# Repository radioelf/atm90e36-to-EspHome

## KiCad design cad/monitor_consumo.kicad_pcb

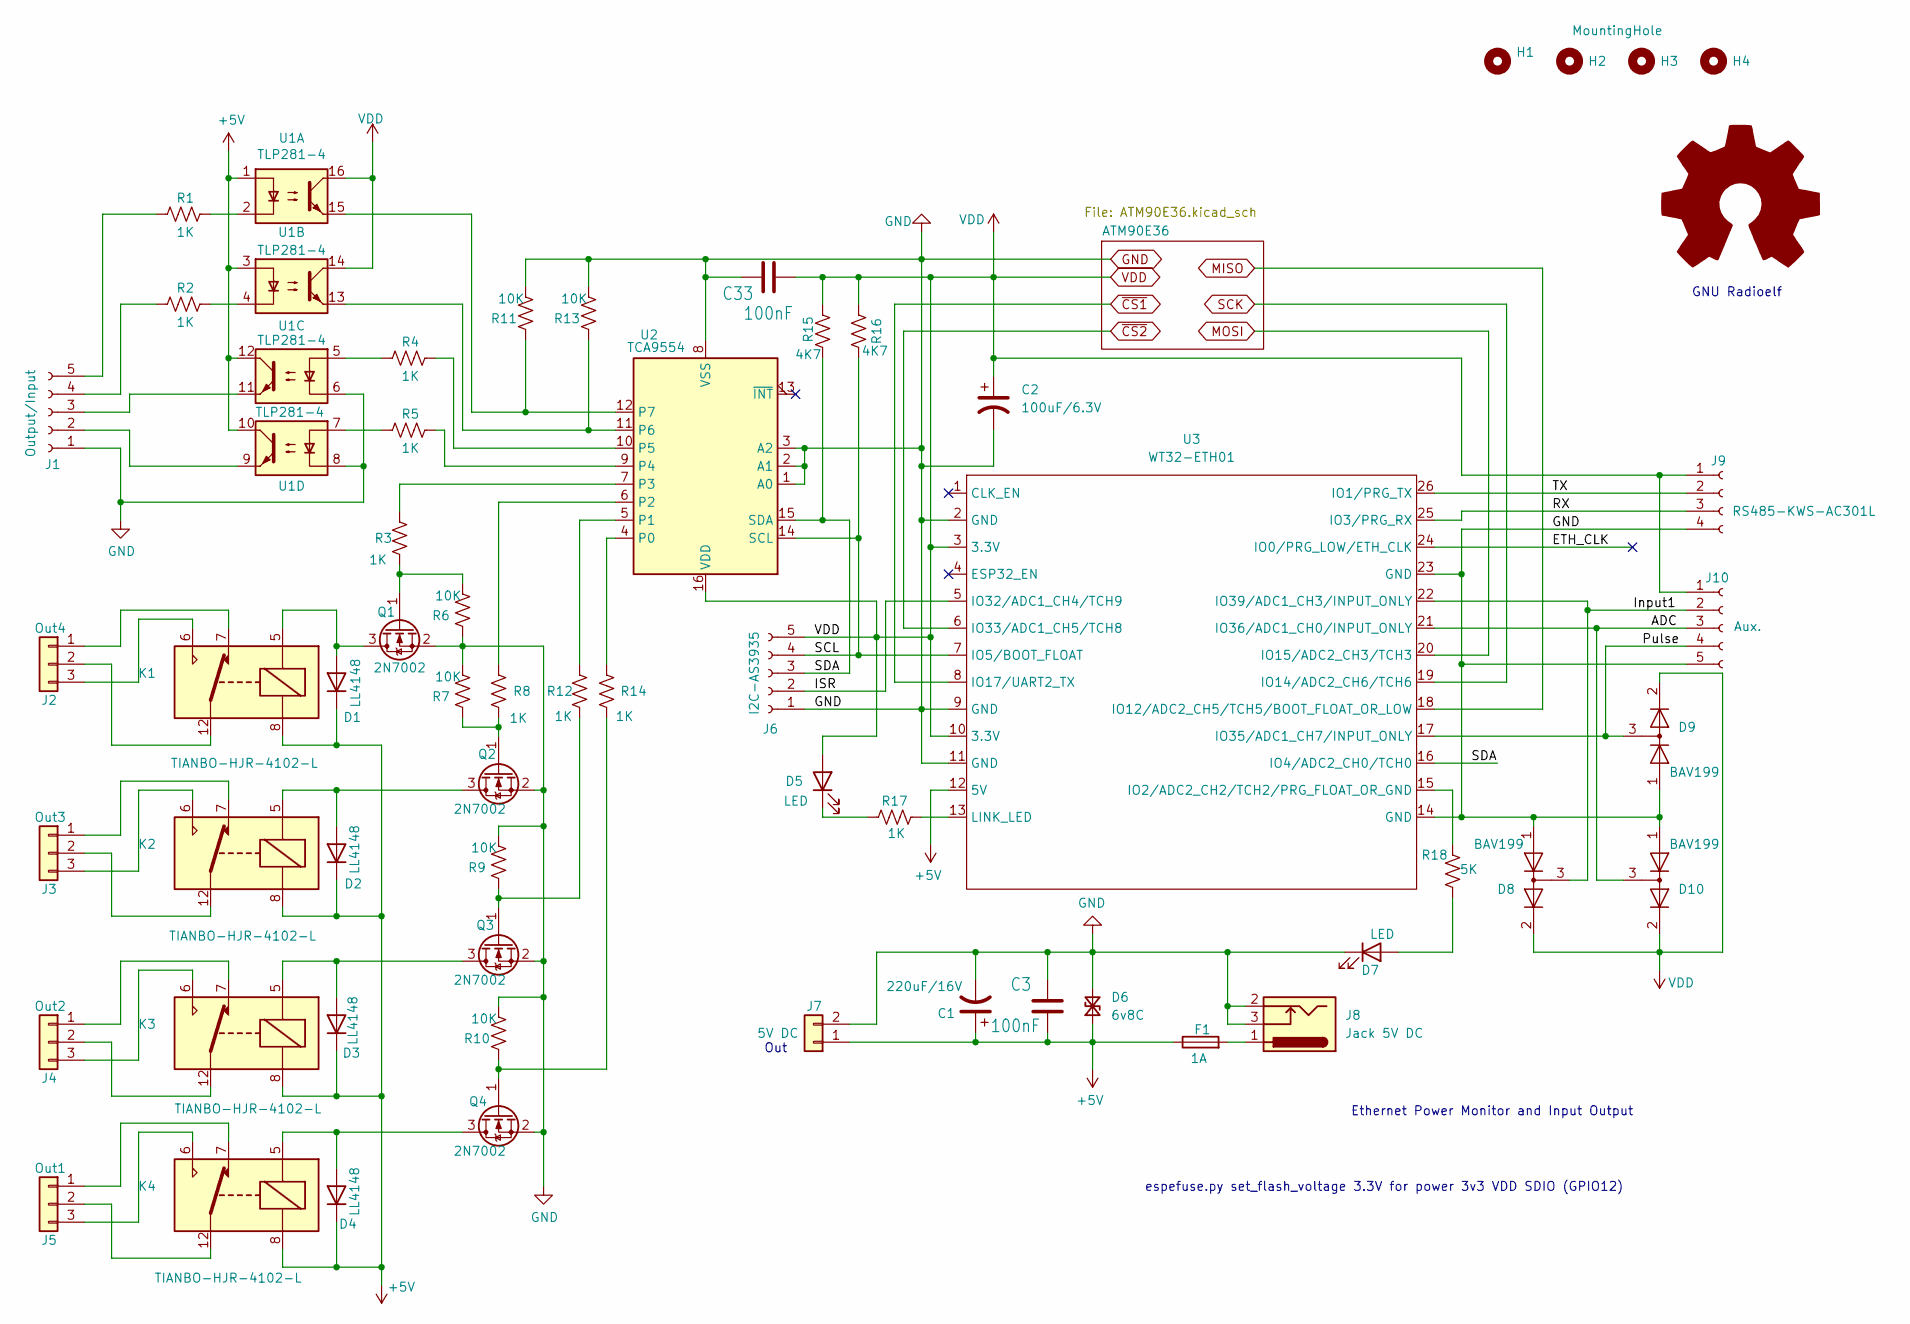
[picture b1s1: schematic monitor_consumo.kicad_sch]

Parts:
C1: 220uF/16V; CP_Elec_8x5.4
C2: 100uF/6.3V; CP_Elec_4x5.4
C3, C33: 100nF; C0603
D1, D2, D3, D4: LL4148; D_MiniMELF
D5, D7: LED; LED_0603_1608Metric
D6: 6v8C; D_SMB
D8, D9, D10: BAV199; SOT-23
F1: 1A; Fuseholder_TR5_Littelfuse_No560_No460
H1, H2, H3, H4: MountingHole; MountingHole_3.2mm_M3
J1: Output/Input; PinHeader_1x05_P2.54mm_Vertical
J2: Out4; TerminalBlock_Phoenix_PT-1,5-3-3.5-H_1x03_P3.50mm_Horizontal
J3: Out3; TerminalBlock_Phoenix_PT-1,5-3-3.5-H_1x03_P3.50mm_Horizontal
J4: Out2; TerminalBlock_Phoenix_PT-1,5-3-3.5-H_1x03_P3.50mm_Horizontal
J5: Out1; TerminalBlock_Phoenix_PT-1,5-3-3.5-H_1x03_P3.50mm_Horizontal
J6: I2C-AS3935; PinHeader_1x05_P2.54mm_Vertical
J7: 5V DC; JST_NV_B02P-NV_1x02_P5.00mm_Vertical
J8: Jack 5V DC; BarrelJack_GCT_DCJ200-10-A_Horizontal
J9: RS485-KWS-AC301L; PinHeader_1x04_P2.54mm_Vertical
J10: Aux.; PinHeader_1x05_P2.54mm_Vertical
K1, K2, K3, K4: TIANBO-HJR-4102-L; Relay_SPDT_HJR-4102
Q1, Q2, Q3, Q4: 2N7002; 2N7002-SOT95P240X111-3N
R1, R2, R3, R4, R5, R8, R12, R14, R17: 1K; R0603
R6, R7, R9, R10, R11, R13: 10K; R0603
R15, R16: 4K7; R0603
R18: 5K; R0603
U1: TLP281-4; SOIC127P700X210-16N
U2: TCA9554; SOIC-16W_7.5x10.3mm_P1.27mm
U3: WT32-ETH01

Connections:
+5V: C1.1, C3.2, D1.1 (K), D2.1 (K), D3.1 (K), D4.1 (K), D6.1 (A1), F1.1, J7.1, K1.8, K2.8, K3.8, K4.8, U1.1, U1.3, U1.10, U1.12, U3.12 (5V)
/ADC: D10.3 (K), J10.3, U3.21 (IO36/ADC1_CH0/INPUT_ONLY)
/ETH_CLK: U3.24 (IO0/PRG_LOW/ETH_CLK)
/ISR: J6.2, U3.5 (IO32/ADC1_CH4/TCH9)
/Input1: D8.3 (K), J10.2, U3.22 (IO39/ADC1_CH3/INPUT_ONLY)
/Pulse: D9.3 (K), J10.4, U3.17 (IO35/ADC1_CH7/INPUT_ONLY)
/RX: J9.3, U3.25 (IO3/PRG_RX)
/SCL: J6.4, R16.1, U2.14 (SCL), U3.7 (IO5/BOOT_FLOAT)
/SDA: J6.3, R15.1, U2.15 (SDA), U3.16 (IO4/ADC2_CH0/TCH0)
/TX: J9.2, U3.26 (IO1/PRG_TX)
GND: C1.2, C2.2, C3.1, C33.1, D6.2 (A2), D7.1 (K), D8.1 (K), D9.1 (K), D10.1 (K), J1.1, J6.1, J7.2, J8.2, J8.3, J9.4, J10.5, Q1.2 (S), Q2.2 (S), Q3.2 (S), Q4.2 (S), R6.1, R7.2, R9.2, R10.2, R11.2, R13.2, U1.6, U1.8, U2.1 (A0), U2.2 (A1), U2.3 (A2), U2.8 (VSS), U3.2 (GND), U3.9 (GND), U3.11 (GND), U3.14 (GND), U3.23 (GND); also elsewhere on the board
MISO: U3.18 (IO12/ADC2_CH5/TCH5/BOOT_FLOAT_OR_LOW); also elsewhere on the board
MOSI: U3.20 (IO15/ADC2_CH3/TCH3); also elsewhere on the board
unnamed: D1.2 (A), K1.5, Q1.3 (D)
unnamed: D2.2 (A), K2.5, Q2.3 (D)
unnamed: D3.2 (A), K3.5, Q3.3 (D)
unnamed: D4.2 (A), K4.5, Q4.3 (D)
unnamed: D5.1 (K), R17.1
unnamed: D7.2 (A), R18.1
unnamed: F1.2, J8.1
unnamed: J1.2, U1.9
unnamed: J1.3, U1.11
unnamed: J1.4, R2.2
unnamed: J1.5, R1.2
unnamed: J2.1, K1.7
unnamed: J2.2, K1.1, K1.12
unnamed: J2.3, K1.6
unnamed: J3.1, K2.7
unnamed: J3.2, K2.1, K2.12
unnamed: J3.3, K2.6
unnamed: J4.1, K3.7
unnamed: J4.2, K3.1, K3.12
unnamed: J4.3, K3.6
unnamed: J5.1, K4.7
unnamed: J5.2, K4.1, K4.12
unnamed: J5.3, K4.6
unnamed: Q1.1 (G), R3.1, R6.2
unnamed: Q2.1 (G), R7.1, R8.1
unnamed: Q3.1 (G), R9.1, R12.1
unnamed: Q4.1 (G), R10.1, R14.1
unnamed: R1.1, U1.2
unnamed: R2.1, U1.4
unnamed: R4.2, U1.5
unnamed: R5.2, U1.7
unnamed: R14.2, U2.4 (P0)
unnamed: R12.2, U2.5 (P1)
unnamed: R8.2, U2.6 (P2)
unnamed: R3.2, U2.7 (P3)
unnamed: R5.1, U2.9 (P4)
unnamed: R4.1, U2.10 (P5)
unnamed: R13.1, U1.13, U2.11 (P6)
unnamed: R11.1, U1.15, U2.12 (P7)
unnamed: R18.2, U3.15 (IO2/ADC2_CH2/TCH2/PRG_FLOAT_OR_GND)
unnamed: R17.2, U3.13 (LINK_LED)
SCK: U3.19 (IO14/ADC2_CH6/TCH6); also elsewhere on the board
VDD: C2.1, C33.2, D5.2 (A), D8.2 (A), D9.2 (A), D10.2 (A), J6.5, J9.1, J10.1, R15.2, R16.2, U1.14, U1.16, U2.16 (VDD), U3.3 (3.3V), U3.10 (3.3V); also elsewhere on the board
~CS1: U3.8 (IO17/UART2_TX); also elsewhere on the board
~CS2: U3.6 (IO33/ADC1_CH5/TCH8); also elsewhere on the board

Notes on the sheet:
GNU Radioelf
espefuse.py set_flash_voltage 3.3V for power 3v3 VDD SDIO (GPIO12)
Out
Ethernet Power Monitor and Input Output

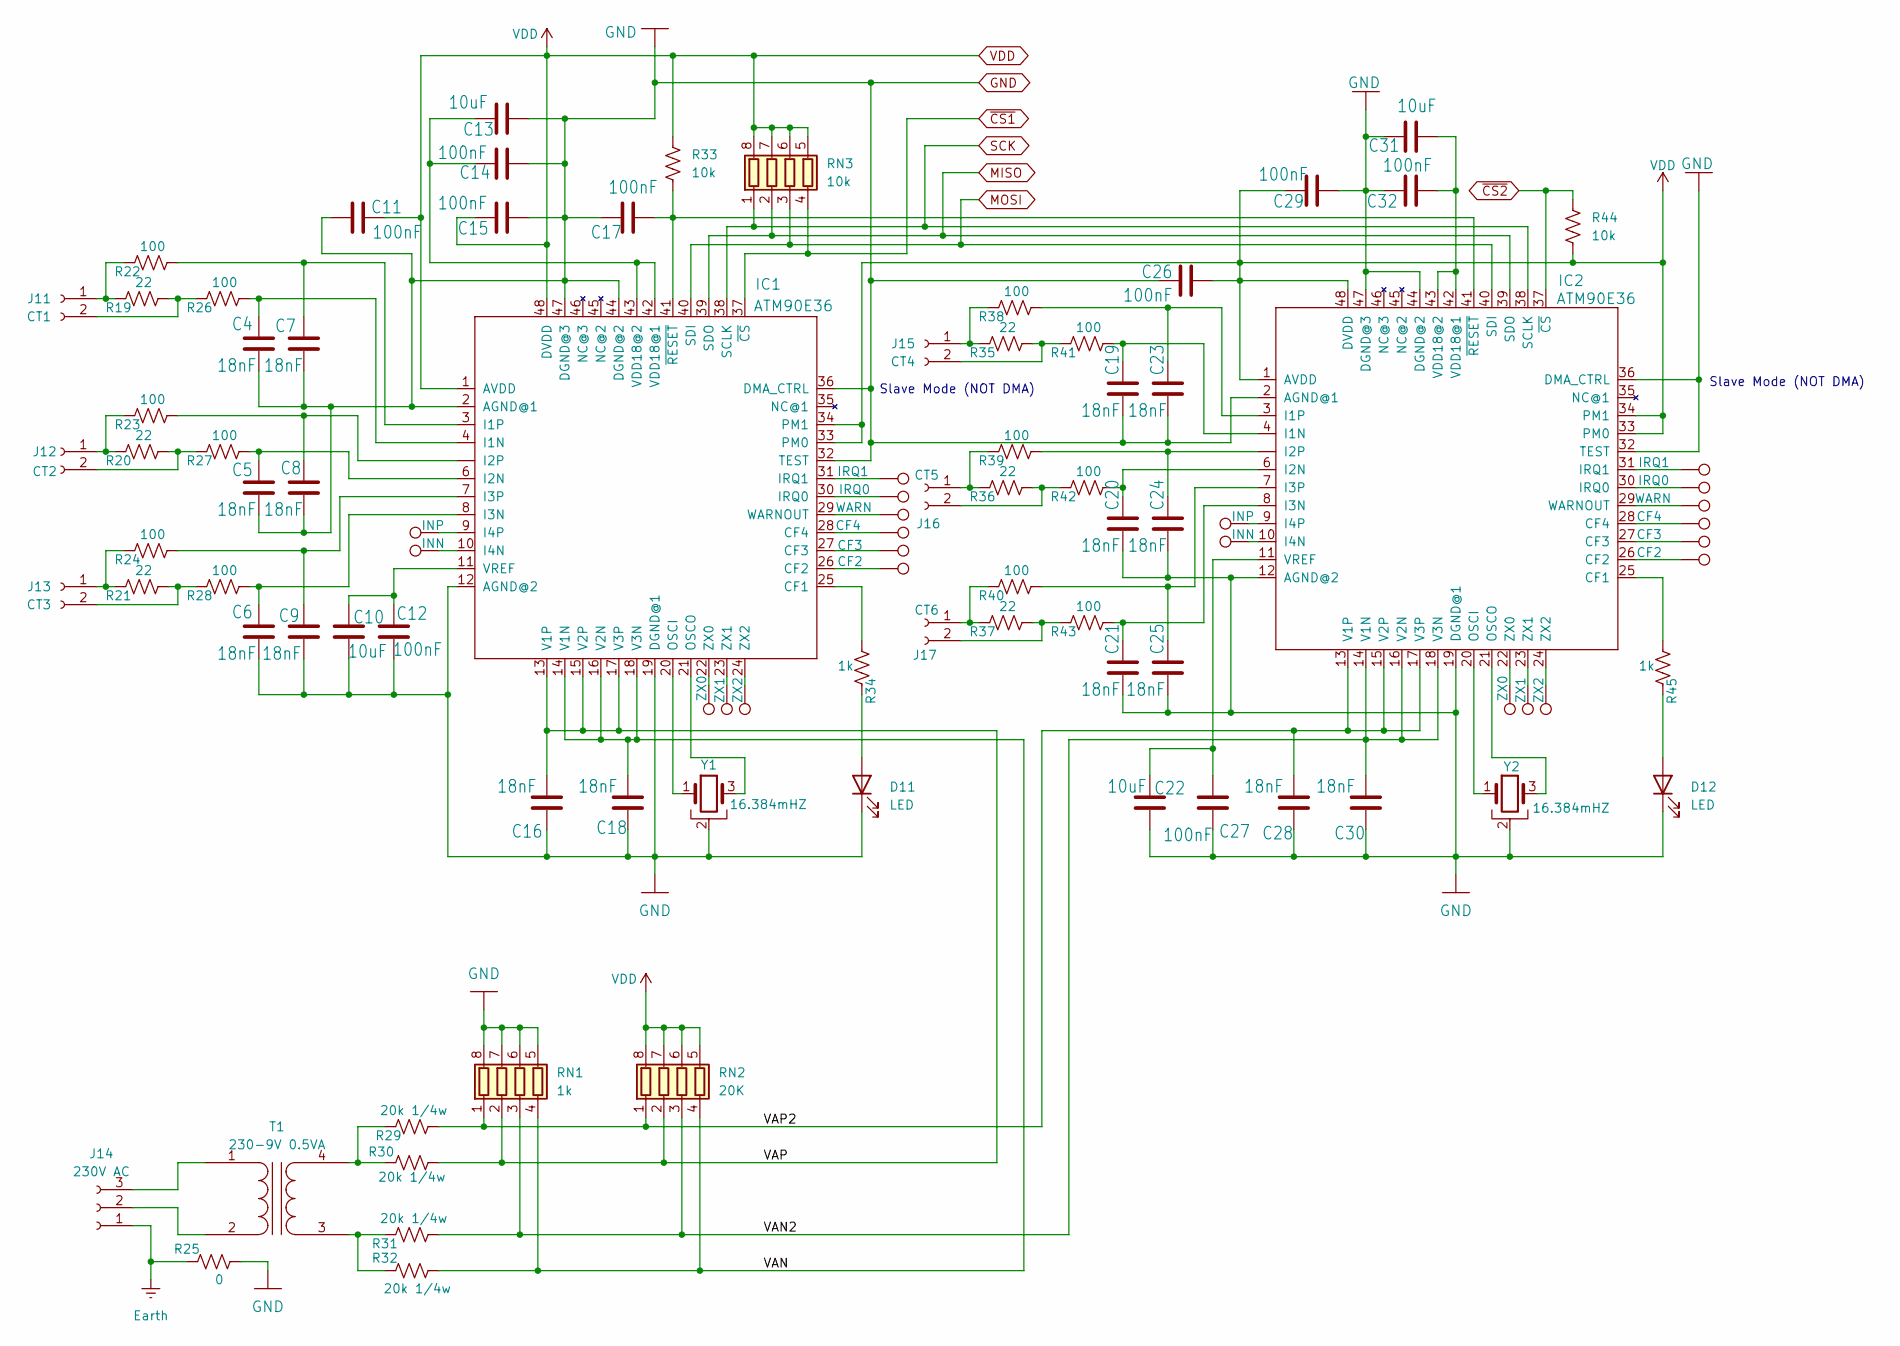
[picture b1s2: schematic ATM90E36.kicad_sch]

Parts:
C4, C5, C6, C7, C8, C9, C16, C18, C19, C20, C21, C23, C24, C25, C28, C30: 18nF; C0603
C10, C13, C22, C31: 10uF; C0603
C11, C12, C14, C15, C17, C26, C27, C29, C32: 100nF; C0603
D11, D12: LED; LED_0603_1608Metric
IC1, IC2: ATM90E36; TQFP48
J11: CT1; TerminalBlock_Phoenix_PT-1,5-2-3.5-H_1x02_P3.50mm_Horizontal
J12: CT2; TerminalBlock_Phoenix_PT-1,5-2-3.5-H_1x02_P3.50mm_Horizontal
J13: CT3; TerminalBlock_Phoenix_PT-1,5-2-3.5-H_1x02_P3.50mm_Horizontal
J14: 230V AC; JST_NV_B03P-NV_1x03_P5.00mm_Vertical
J15: CT4; TerminalBlock_Phoenix_PT-1,5-2-3.5-H_1x02_P3.50mm_Horizontal
J16: CT5; TerminalBlock_Phoenix_PT-1,5-2-3.5-H_1x02_P3.50mm_Horizontal
J17: CT6; TerminalBlock_Phoenix_PT-1,5-2-3.5-H_1x02_P3.50mm_Horizontal
R19, R20, R21, R35, R36, R37: 22; R0603
R22, R23, R24, R26, R27, R28, R38, R39, R40, R41, R42, R43: 100; R0603
R25: 0; R0603
R29, R30, R31, R32: 20k 1/4w; R_1206_3216Metric
R33, R44: 10k; R0603
R34, R45: 1k; R0603
RN1: 1k; RA1206-8
RN2: 20K; RA1206-8
RN3: 10k; RA1206-8
T1: 230-9V 0.5VA; Transformer_hr-diemen-efiter_E2010054
TP1, TP12: INP; TestPoint_THTPad_1.5x1.5mm_Drill0.7mm
TP2, TP13: INN; TestPoint_THTPad_1.5x1.5mm_Drill0.7mm
TP3, TP14: ZX0; TestPoint_THTPad_1.5x1.5mm_Drill0.7mm
TP4, TP15: ZX1; TestPoint_Pad_1.0x1.0mm
TP5, TP16: ZX2; TestPoint_Pad_1.0x1.0mm
TP6, TP17: IRQ1; TestPoint_Pad_1.0x1.0mm
TP7, TP18: IRQ0; TestPoint_THTPad_1.5x1.5mm_Drill0.7mm
TP8, TP19: WARN; TestPoint_Pad_1.0x1.0mm
TP9, TP20: CF4; TestPoint_Pad_1.0x1.0mm
TP10, TP21: CF3; TestPoint_Pad_1.0x1.0mm
TP11, TP22: CF2; TestPoint_Pad_1.0x1.0mm
Y1, Y2: 16.384mHZ; Crystal_SMD_EuroQuartz_MT-4Pin_3.2x2.5mm_HandSoldering

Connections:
/ATM90E36/VAN: C18.1, IC1.14 (V1N), IC1.16 (V2N), IC1.18 (V3N), R32.2, RN1.4 (R4.1), RN2.4 (R4.1)
/ATM90E36/VAN2: C30.1, IC2.14 (V1N), IC2.16 (V2N), IC2.18 (V3N), R31.2, RN1.3 (R3.1), RN2.3 (R3.1)
/ATM90E36/VAP: C16.1, IC1.13 (V1P), IC1.15 (V2P), IC1.17 (V3P), R30.2, RN1.2 (R2.1), RN2.2 (R2.1)
/ATM90E36/VAP2: C28.1, IC2.13 (V1P), IC2.15 (V2P), IC2.17 (V3P), R29.2, RN1.1 (R1.1), RN2.1 (R1.1)
Earth: J14.1, R25.1
GND: C4.1, C5.1, C6.1, C7.1, C8.1, C9.1, C10.2, C11.1, C12.2, C13.1, C14.1, C15.1, C16.2, C17.1, C18.2, C19.1, C20.1, C21.1, C22.2, C23.1, C24.1, C25.1, C26.1, C27.2, C28.2, C29.1, C30.2, C31.2, C32.2, D11.1 (K), D12.1 (K), IC1.2 (AGND@1), IC1.12 (AGND@2), IC1.19 (DGND@1), IC1.32 (TEST), IC1.36 (DMA_CTRL), IC1.44 (DGND@2), IC1.47 (DGND@3), IC2.2 (AGND@1), IC2.12 (AGND@2), IC2.19 (DGND@1), IC2.32 (TEST), IC2.36 (DMA_CTRL), IC2.44 (DGND@2), IC2.47 (DGND@3), R25.2, RN1.5 (R4.2), RN1.6 (R3.2), RN1.7 (R2.2), RN1.8 (R1.2), Y1.2, Y1.4, Y2.2, Y2.4; also elsewhere on the board
MISO: IC1.39 (SDO), IC2.39 (SDO), RN3.2 (R2.1); also elsewhere on the board
MOSI: IC1.40 (SDI), IC2.40 (SDI), RN3.3 (R3.1); also elsewhere on the board
unnamed: D11.2 (A), R34.1
unnamed: D12.2 (A), R45.1
unnamed: IC1.25 (CF1), R34.2
unnamed: IC1.26 (CF2), TP11.1
unnamed: IC1.27 (CF3), TP10.1
unnamed: IC1.28 (CF4), TP9.1
unnamed: C4.2, IC1.4 (I1N), R26.2
unnamed: C7.2, IC1.3 (I1P), R22.2
unnamed: C5.2, IC1.6 (I2N), R27.2
unnamed: C8.2, IC1.5 (I2P), R23.2
unnamed: C6.2, IC1.8 (I3N), R28.2
unnamed: C9.2, IC1.7 (I3P), R24.2
unnamed: IC1.10 (I4N), TP2.1
unnamed: IC1.9 (I4P), TP1.1
unnamed: IC1.30 (IRQ0), TP7.1
unnamed: IC1.31 (IRQ1), TP6.1
unnamed: IC1.20 (OSCI), Y1.1
unnamed: IC1.21 (OSCO), Y1.3
unnamed: C13.2, C14.2, IC1.42 (VDD18@1), IC1.43 (VDD18@2)
unnamed: C10.1, C12.1, IC1.11 (VREF)
unnamed: IC1.29 (WARNOUT), TP8.1
unnamed: IC1.22 (ZX0), TP3.1
unnamed: IC1.23 (ZX1), TP4.1
unnamed: IC1.24 (ZX2), TP5.1
unnamed: C17.2, IC1.41 (~RESET), IC2.41 (~RESET), R33.2
unnamed: IC2.25 (CF1), R45.2
unnamed: IC2.26 (CF2), TP22.1
unnamed: IC2.27 (CF3), TP21.1
unnamed: IC2.28 (CF4), TP20.1
unnamed: C19.2, IC2.4 (I1N), R41.2
unnamed: C23.2, IC2.3 (I1P), R38.2
unnamed: C20.2, IC2.6 (I2N), R42.2
unnamed: C24.2, IC2.5 (I2P), R39.2
unnamed: C21.2, IC2.8 (I3N), R43.2
unnamed: C25.2, IC2.7 (I3P), R40.2
unnamed: IC2.10 (I4N), TP13.1
unnamed: IC2.9 (I4P), TP12.1
unnamed: IC2.30 (IRQ0), TP18.1
unnamed: IC2.31 (IRQ1), TP17.1
unnamed: IC2.20 (OSCI), Y2.1
unnamed: IC2.21 (OSCO), Y2.3
unnamed: C31.1, C32.1, IC2.42 (VDD18@1), IC2.43 (VDD18@2)
unnamed: C22.1, C27.1, IC2.11 (VREF)
unnamed: IC2.29 (WARNOUT), TP19.1
unnamed: IC2.22 (ZX0), TP14.1
unnamed: IC2.23 (ZX1), TP15.1
unnamed: IC2.24 (ZX2), TP16.1
unnamed: J11.1, R19.1, R22.1
unnamed: J11.2, R19.2, R26.1
unnamed: J12.1, R20.1, R23.1
unnamed: J12.2, R20.2, R27.1
unnamed: J13.1, R21.1, R24.1
unnamed: J13.2, R21.2, R28.1
unnamed: J14.2, T1.2 (AB)
unnamed: J14.3, T1.1 (AA)
unnamed: J15.1, R35.1, R38.1
unnamed: J15.2, R35.2, R41.1
unnamed: J16.1, R36.1, R39.1
unnamed: J16.2, R36.2, R42.1
unnamed: J17.1, R37.1, R40.1
unnamed: J17.2, R37.2, R43.1
unnamed: R31.1, R32.1, T1.3 (SA)
unnamed: R29.1, R30.1, T1.4 (SB)
SCK: IC1.38 (SCLK), IC2.38 (SCLK), RN3.1 (R1.1); also elsewhere on the board
VDD: C11.2, C15.2, C26.2, C29.2, IC1.1 (AVDD), IC1.33 (PM0), IC1.34 (PM1), IC1.48 (DVDD), IC2.1 (AVDD), IC2.33 (PM0), IC2.34 (PM1), IC2.48 (DVDD), R33.1, R44.1, RN2.5 (R4.2), RN2.6 (R3.2), RN2.7 (R2.2), RN2.8 (R1.2), RN3.5 (R4.2), RN3.6 (R3.2), RN3.7 (R2.2), RN3.8 (R1.2); also elsewhere on the board
~CS1: IC1.37 (~CS), RN3.4 (R4.1); also elsewhere on the board
~CS2: IC2.37 (~CS), R44.2; also elsewhere on the board

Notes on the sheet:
Slave Mode (NOT DMA)

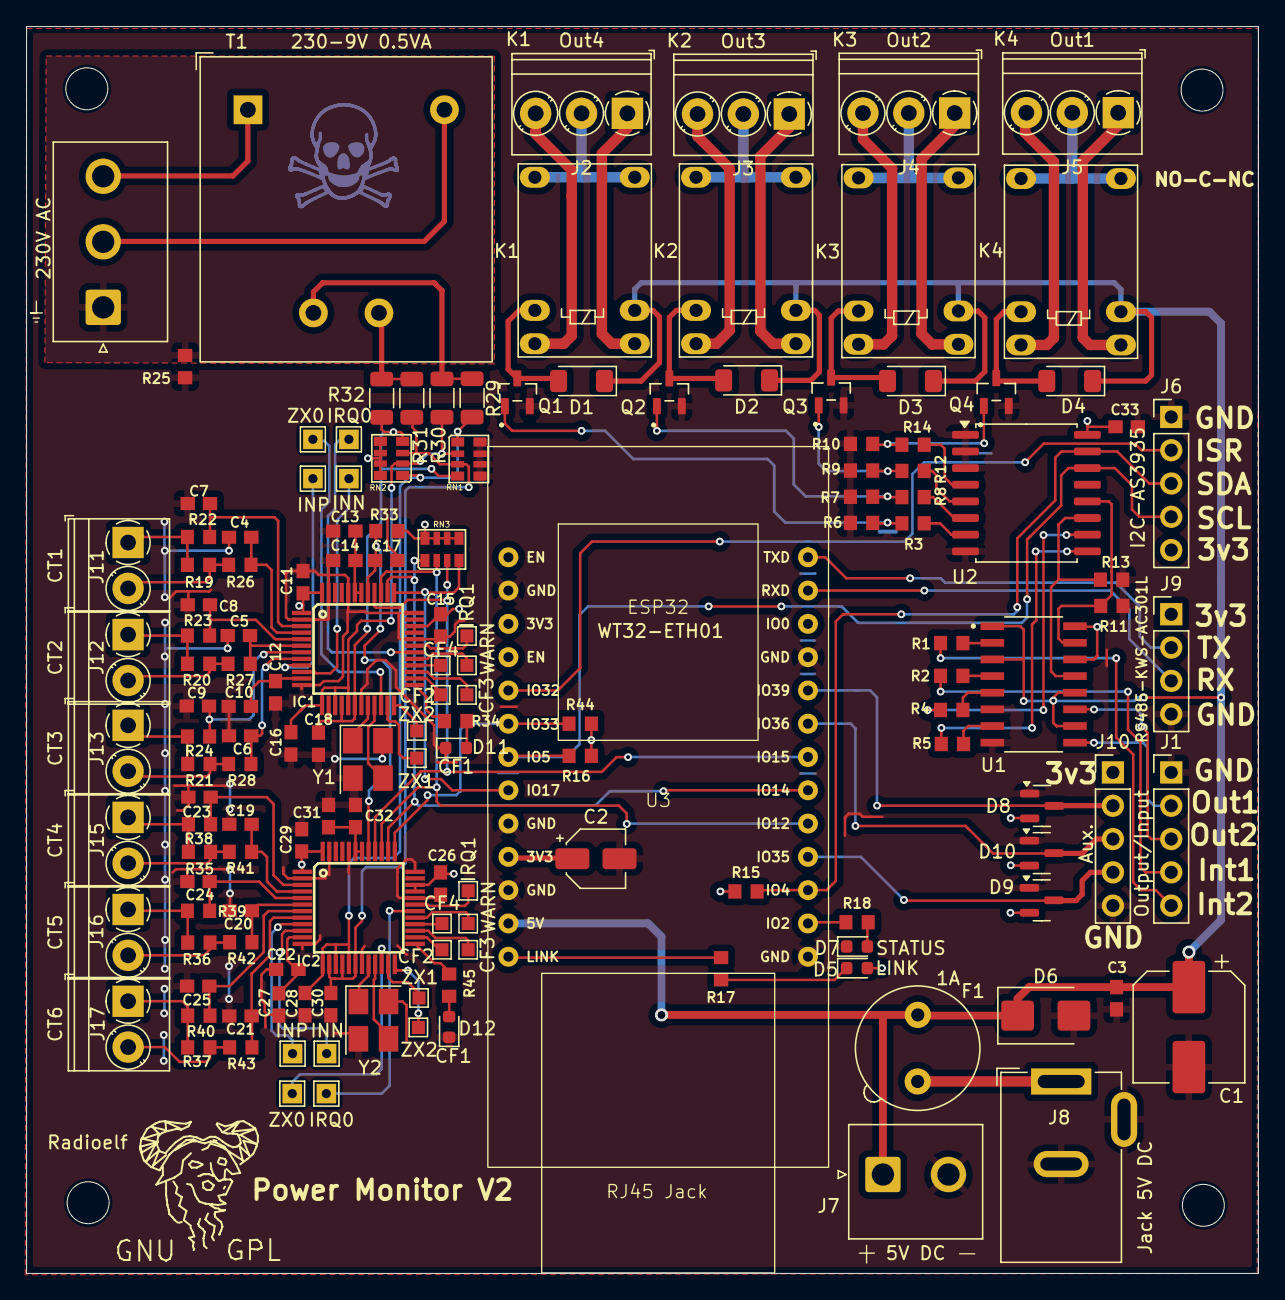
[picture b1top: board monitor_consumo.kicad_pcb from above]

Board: 2 copper layers, 94.0 x 95.1 mm, 154 parts (0 on the bottom side), 125 nets.

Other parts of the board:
Radioelf: GNU-Logo; Symbol_GNU-Logo_SilkscreenTop

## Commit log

2024-12-29 Create Rename
2024-12-29 Update Rename
